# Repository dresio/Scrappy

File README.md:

# Scrappy
A basic platform for robot companions using commonly found or easily obtainable parts. It is designed to work in modules that can be switched in and out depending on avaialble parts and project requirements. All mechanical parts are prioritized to be 3D printable and assembled with M3 bolts and nuts. 
Source files are developed in Solidworks and KiCad.

The rest of this is a live document on development of the project. Design requirements will be changed when further clarification of the projects development is needed. Everything else outlines further developement goals for the project to reach the so called final product.

## Design Requirements
1. All parts will be able to be sourced to be common parts that can be obtained relativly simply
2. Any non-sourced parts will be designed to be 3D printed. Some parts may also be able to be laser cut. Goal bed size is around 18cm cubed (Prusa MINI print size)
3. Modular support for multiple platforms depending on needs. Any of each part should be able to be replaced by another without switching any other parts. (Ex. Switch processing module from a microcontroller to a computer without replacing any motors, batteries, etc)
4. Electrical modules will communicate over CAN Bus. A standard connection should be used for all modules to make it rapidly expandable. A terminator resistor jumper will be on all modules so it can start or end anywhere. 

## Currently Under Development
* Scrappy Core and Main Mechanical Components
* Jetson Nano Codebase
* Mini SLA (Sealed Lead Acid) Battery Support
* Stepper Motor Support
* Hobby Servo Support
* ROS Support

## System Support Goals:
### Batteries
* SLA or LiFePo Batteries(12V or 24V)
* LiPo Batteries (2-6s)
* Lion Batteries (3-8s)

### Controllers
* Arduino Supported Microcontrollers (Focusing on Teensy Series)
* Raspberry Pi
* Jetson Nano

### Acuators
* Hobby Servos
* DC Motors
* Brushless Motors
* Stepper Motors

### Sensors
* Camera for Raspberry Pi and Jetson Nano
* Raspberry Pi Lidar

### Software
* ROS (Melodic or Eloquent) implementation
  * Will be updated to Noetic or Foxy when Jetpack gets updated
* CANbus network for modules

### Mechanical
* Core Versions
  * Different Core Modules for Different Battery Types
  * Multiple Core Sizes
* Mobility Attachments
  * Mount to Bottom of Core for Motors or Servos
* Sensor Attachments
  * Mount to sides and top of Core
* Display Attachments
  * Mounts to sides and top of Core
* Core Shell
  * Mounts Over Core and can simplify Sensor and Display Attachemnts

### Electrical
* Power Distribution System (Scaled with CANbus Network)
* DC Motor Controller Using H-Bridge
* Raspberry Pi and Jetson Nano Breakout (Hat)
* Arduino Teensy Breakout

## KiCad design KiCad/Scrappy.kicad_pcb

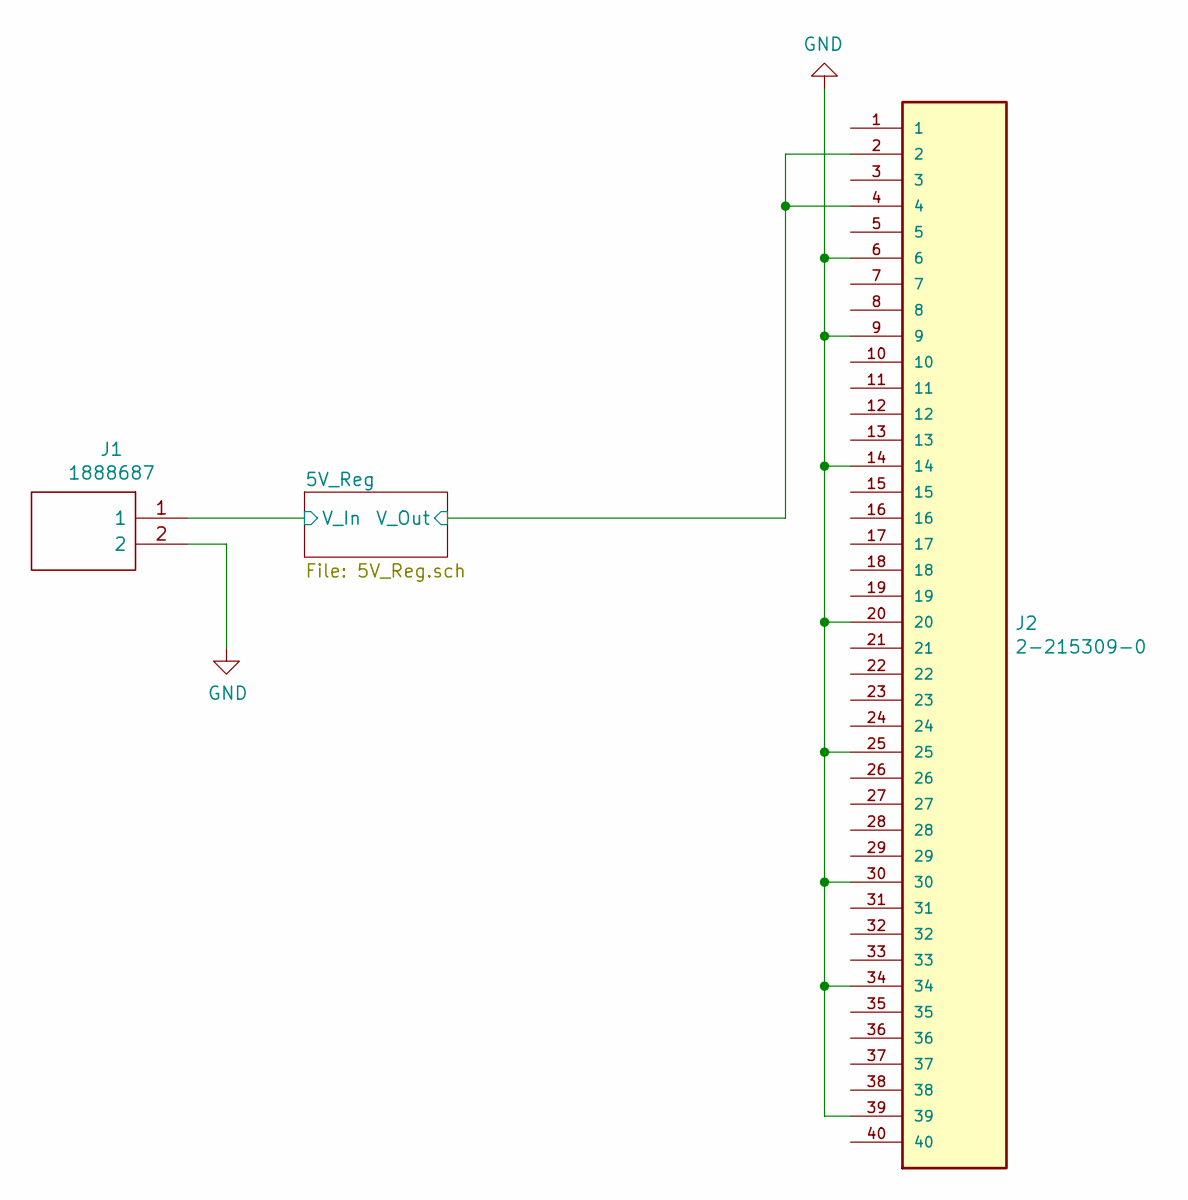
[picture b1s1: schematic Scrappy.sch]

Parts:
J1: 1888687; SHDR2W90P0X508_1X2_1016X950X1500P; Mouser Part Number 651-1888687
J2: 2-215309-0; TE_2-215309-0

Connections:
/5V_Reg/V_In: J1.1; also elsewhere on the board
/5V_Reg/V_Out: J2.2, J2.4; also elsewhere on the board
GND: J1.2, J2.6, J2.9, J2.14, J2.20, J2.25, J2.30, J2.34, J2.39; also elsewhere on the board

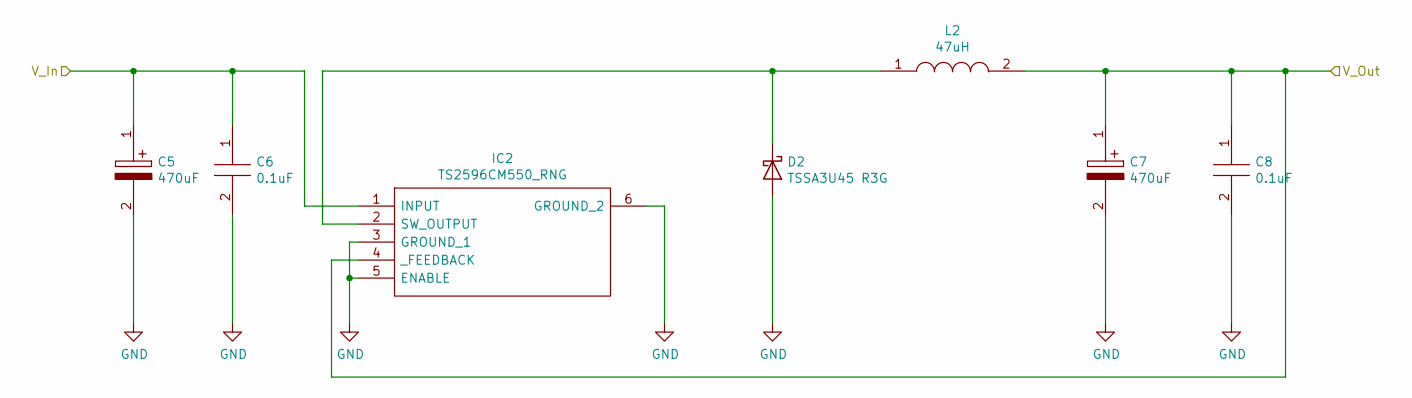
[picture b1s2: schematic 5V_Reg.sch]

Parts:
C1, C3: 470uF; CAPPRD525W60D1025H1750; Digi-Key Part Number 1572-1152-ND
C2, C4: 0.1uF; CAPC1608X90N; Digi-Key Part Number 445-5667-1-ND
D1: TSSA3U45 R3G; D_SMA
IC1: TS2596CM550_RNG; TS2596CM550RNG; Mouser Part Number 821-TS2596CM550RNG
L1: 47uH; INDPM110100X400N; Digi-Key Part Number SRP1038A-470M

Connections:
/5V_Reg/V_In: C1.1, C2.1, IC1.1 (INPUT); also elsewhere on the board
/5V_Reg/V_Out: C3.1, C4.1, IC1.4 (_FEEDBACK), L1.2; also elsewhere on the board
GND: C1.2, C2.2, C3.2, C4.2, D1.2 (A), IC1.3 (GROUND_1), IC1.5 (ENABLE), IC1.6 (GROUND_2); also elsewhere on the board
unnamed: D1.1 (K), IC1.2 (SW_OUTPUT), L1.1

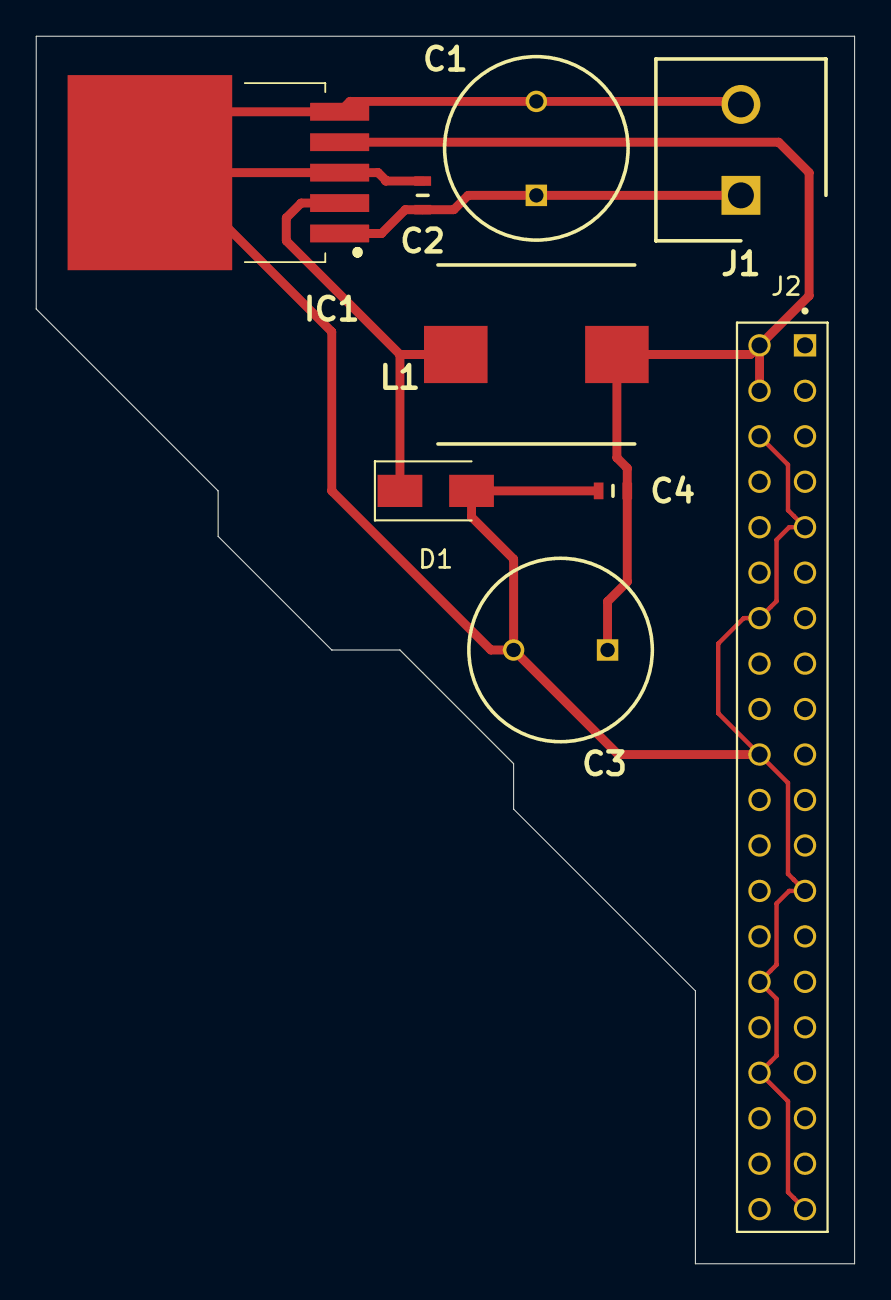
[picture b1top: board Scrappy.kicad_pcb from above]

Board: 2 copper layers, 45.7 x 68.6 mm, 9 parts (0 on the bottom side), 4 nets.

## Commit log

2021-09-07 Outlining Project Goals in Readme
2021-09-20 Initial Commit
    This is the initial commit of content. Solidworks files and KiCad files are added for basic functionality. Many things are still missing and this is in draft form still.
2021-09-21 Motor Update
    More work has done with electronics and hardware for motor connections
2021-10-08 Major changes to mech design
    Previous design looked nice, but required too many moving parts.
    Simplifing parts and properly sourcing hardware helps reduce cost and
    failure points.
2021-10-12 Update Mechanical Structure
    Main update to mechanical superstructure complete. Shell and other smaller components need to be implemented still
2023-03-20 Adding install instructions for OpenCV and basic cpp program for interfacing with the camera module
2023-03-21 Working on build instructions for vision pipeline, added basic core while compiling and cleaned up readme
2023-03-22 Added build system for messages
2023-03-23 Refactoring and documenting. Adding templates to data transport for messages
2023-03-27 Funcional header version of code, may stick with a header library in the long run
